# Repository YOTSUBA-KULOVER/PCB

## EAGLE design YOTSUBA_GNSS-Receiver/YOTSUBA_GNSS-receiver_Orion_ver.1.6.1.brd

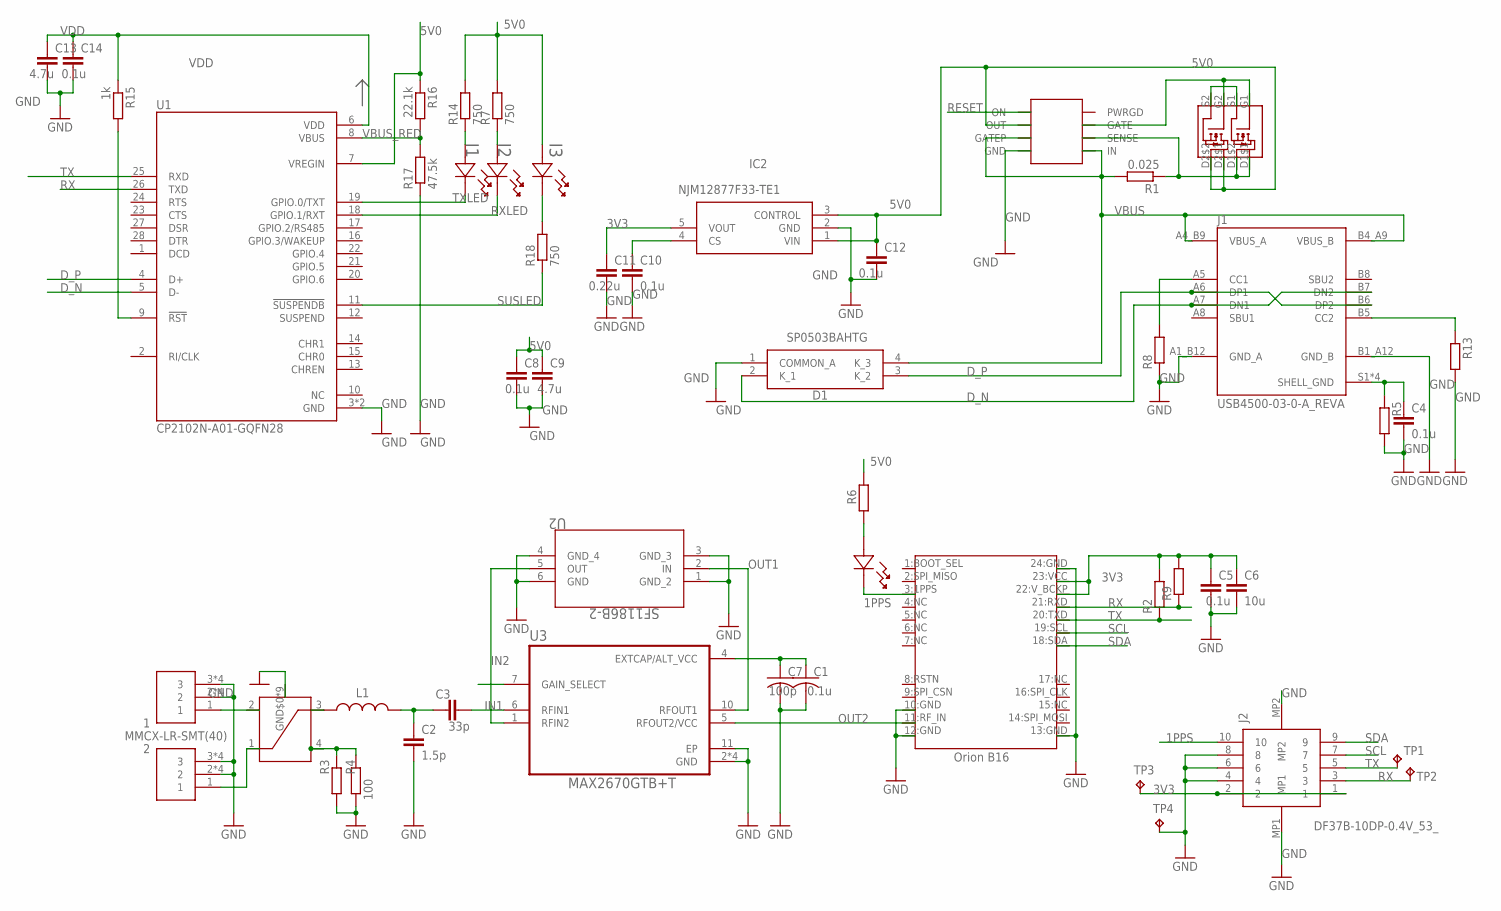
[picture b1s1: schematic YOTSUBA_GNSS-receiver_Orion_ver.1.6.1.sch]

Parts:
1, 2: MMCX-LR-SMT(40)
C1: 0.1u; C1608_OS
C2: 1.5p; C1608
C3: 33p; C1608
C4, C5, C8, C10, C12, C14: 0.1u; C1608
C6: 10u; C1608
C7: 100p; C1608_OS
C9, C13: 4.7u; C1608
C11: 0.22u; C1608
D1: SP0503BAHTG
I1, I2, I3: SML-E12P8WT86; LED_SMLD12_ROM
IC2: NJM12877F33-TE1; SOT95P280X120-5N
J1: USB4500-03-0-A_REVA; GCT_USB4500-03-0-A_REVA
J2: DF37B-10DP-0.4V_53_; DF37B10DP04V53
L1: 4.3n; INDC1608X100N
R1: 0.025; R0603
R2, R5, R6, R8, R9, R13: R-EU_R0603; R0603
R3, R4: 100; R0603
R7, R14, R18: 750; R0603
R10: SML-E12P8WT86; LED_SMLD12_ROM
R15: 1k; R0603
R16: 22.1k; R0603
R17: 47.5k; R0603
TP1, TP2, TP3, TP4: TPTP13SQ; TP13SQ
U1: CP2102N-A01-GQFN28; QFN50P500X500X80-29N
U2: SF1186B-2; SM3030_MUR
U3: MAX2670GTB+T; DFN300X300X80-11N
U$1: ORION_B16
U$3: HC125.A
U$7: DMG6898LSD; SOIC127P600X150-8N
U$8: LTC4361; SOP65P280X100-8N

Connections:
1PPS: J2.10, R10.1, U$1.3:1PPS
3V3: C5.1, C6.1, C11.1, IC2.5 (VOUT), J2.1, J2.2, R2.2, R9.2, TP3.TP, U$1.22:V_BCKP, U$1.23:VCC
5V0: C8.1, C9.1, C12.1, I3.2, IC2.1 (VIN), IC2.3 (CONTROL), R6.2, R7.2, R14.2, R16.1, U1.7 (VREGIN), U$7.D2$1, U$7.D2$2, U$8.OUT
$11: C1.1, C7.1, U3.4 (EXTCAP/ALT_VCC)
D_N: D1.2 (K_1), J1.A7 (DN1), J1.B7 (DN2), U1.5 (D-)
D_P: D1.3 (K_2), J1.A6 (DP1), J1.B6 (DP2), U1.4 (D+)
GND: 1.2, 1.3, 1.4 (2), 1.5 (3), 1.P$1 (2), 1.P$2 (2), 1.P$3 (3), 1.P$4 (3), 2.2, 2.3, 2.4 (2), 2.5 (3), 2.P$1 (2), 2.P$2 (2), 2.P$3 (3), 2.P$4 (3), C1.2, C2.2, C4.2, C5.2, C6.2, C7.2, C8.2, C9.2, C10.2, C11.2, C12.2, C13.2, C14.2, D1.1 (COMMON_A), IC2.2 (GND), J1.A1_B12 (GND_A), J1.B1_A12 (GND_B), J2.4, J2.6, J2.8, J2.MP1, J2.MP2, R3.1, R4.1, R5.2, R8.1, R13.2, R17.1, TP4.TP, U1.3 (GND), U1.29 (GND), U2.1 (GND_2), U2.3 (GND_3), U2.4 (GND_4), U2.6 (GND), U3.2 (GND), U3.3 (GND), U3.8 (GND), U3.9 (GND), U3.11 (EP), U$1.10:GND, U$1.12:GND, U$1.13:GND, U$1.24:GND, U$3.GND$0 (GND), U$3.GND$1 (GND), U$3.GND$2 (GND), U$3.GND$3 (GND), U$3.GND$4 (GND), U$3.GND$5 (GND), U$3.GND$6 (GND), U$3.GND$7 (GND), U$3.GND$8 (GND), U$8.GND
IN1: C3.2, U3.6 (RFIN1)
IN1_2: C2.1, C3.1, L1.2
IN1_3: L1.1, U$3.3
IN2: U2.5 (OUT), U3.1 (RFIN2)
unnamed: 1.1, U$3.2
unnamed: 2.1, U$3.1
unnamed: I3.1, R18.2
unnamed: C10.1, IC2.4 (CS)
unnamed: I2.2, R7.1
unnamed: C4.1, J1.S1 (SHELL_GND), J1.S2 (SHELL_GND), J1.S3 (SHELL_GND), J1.S4 (SHELL_GND), R5.1
unnamed: I1.2, R14.1
unnamed: R3.2, R4.2, U$3.4
unnamed: R6.1, R10.2
unnamed: U$7.S1, U$7.S2
unnamed: R1.1, U$7.D1$1, U$7.D1$2, U$8.SENSE
unnamed: J1.B5 (CC2), R13.1
unnamed: U$7.G1, U$7.G2, U$8.GATE
unnamed: J1.A5 (CC1), R8.2
unnamed: R15.2, U1.9 (!RST)
OUT1: U2.2 (IN), U3.10 (RFOUT1)
OUT2: U3.5 (RFOUT2/VCC), U$1.11:RF_IN
RESET: U$8.ON
RX: J2.3, R9.1, TP2.TP, U1.26 (TXD), U$1.21:RXD
RXLED: I2.1, U1.18 (GPIO.1/RXT)
SCL: J2.7, U$1.19:SCL
SDA: J2.9, U$1.18:SDA
SUSLED: R18.1, U1.11 (!SUSPENDB)
TX: J2.5, R2.1, TP1.TP, U1.25 (RXD), U$1.20:TXD
TXLED: I1.1, U1.19 (GPIO.0/TXT)
VBUS: D1.4 (K_3), J1.A4_B9 (VBUS_A), J1.B4_A9 (VBUS_B), R1.2, U$8.GATEP, U$8.IN
VBUS_RED: R16.2, R17.2, U1.8 (VBUS)
VDD: C13.1, C14.1, R15.1, U1.6 (VDD)

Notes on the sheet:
Orion B16

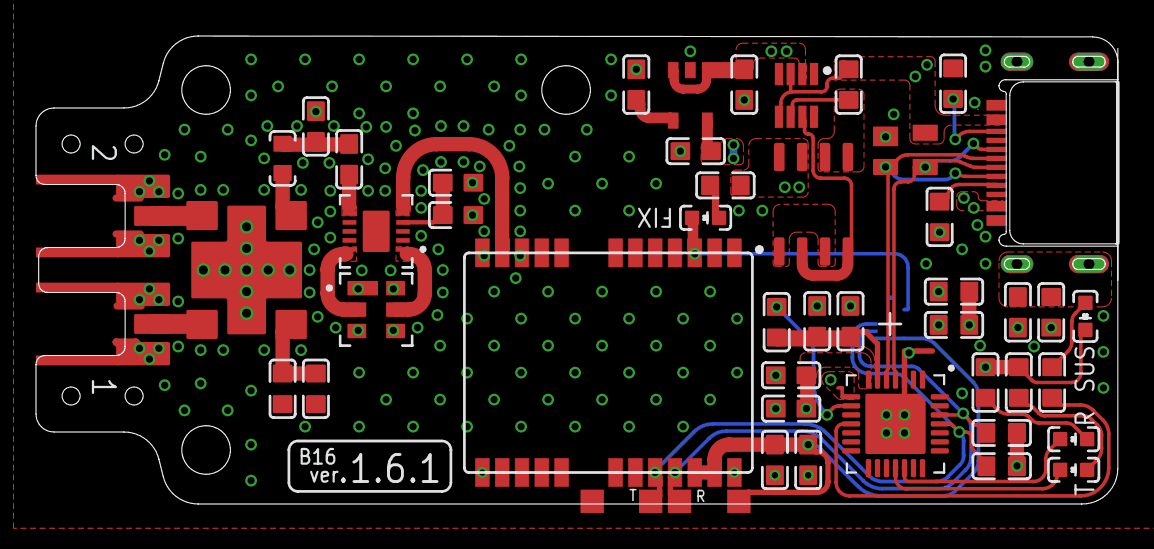
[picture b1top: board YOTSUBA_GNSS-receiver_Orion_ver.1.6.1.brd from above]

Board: 4 copper layers, 60.1 x 26.0 mm, 51 parts (1 on the bottom side), 38 nets.

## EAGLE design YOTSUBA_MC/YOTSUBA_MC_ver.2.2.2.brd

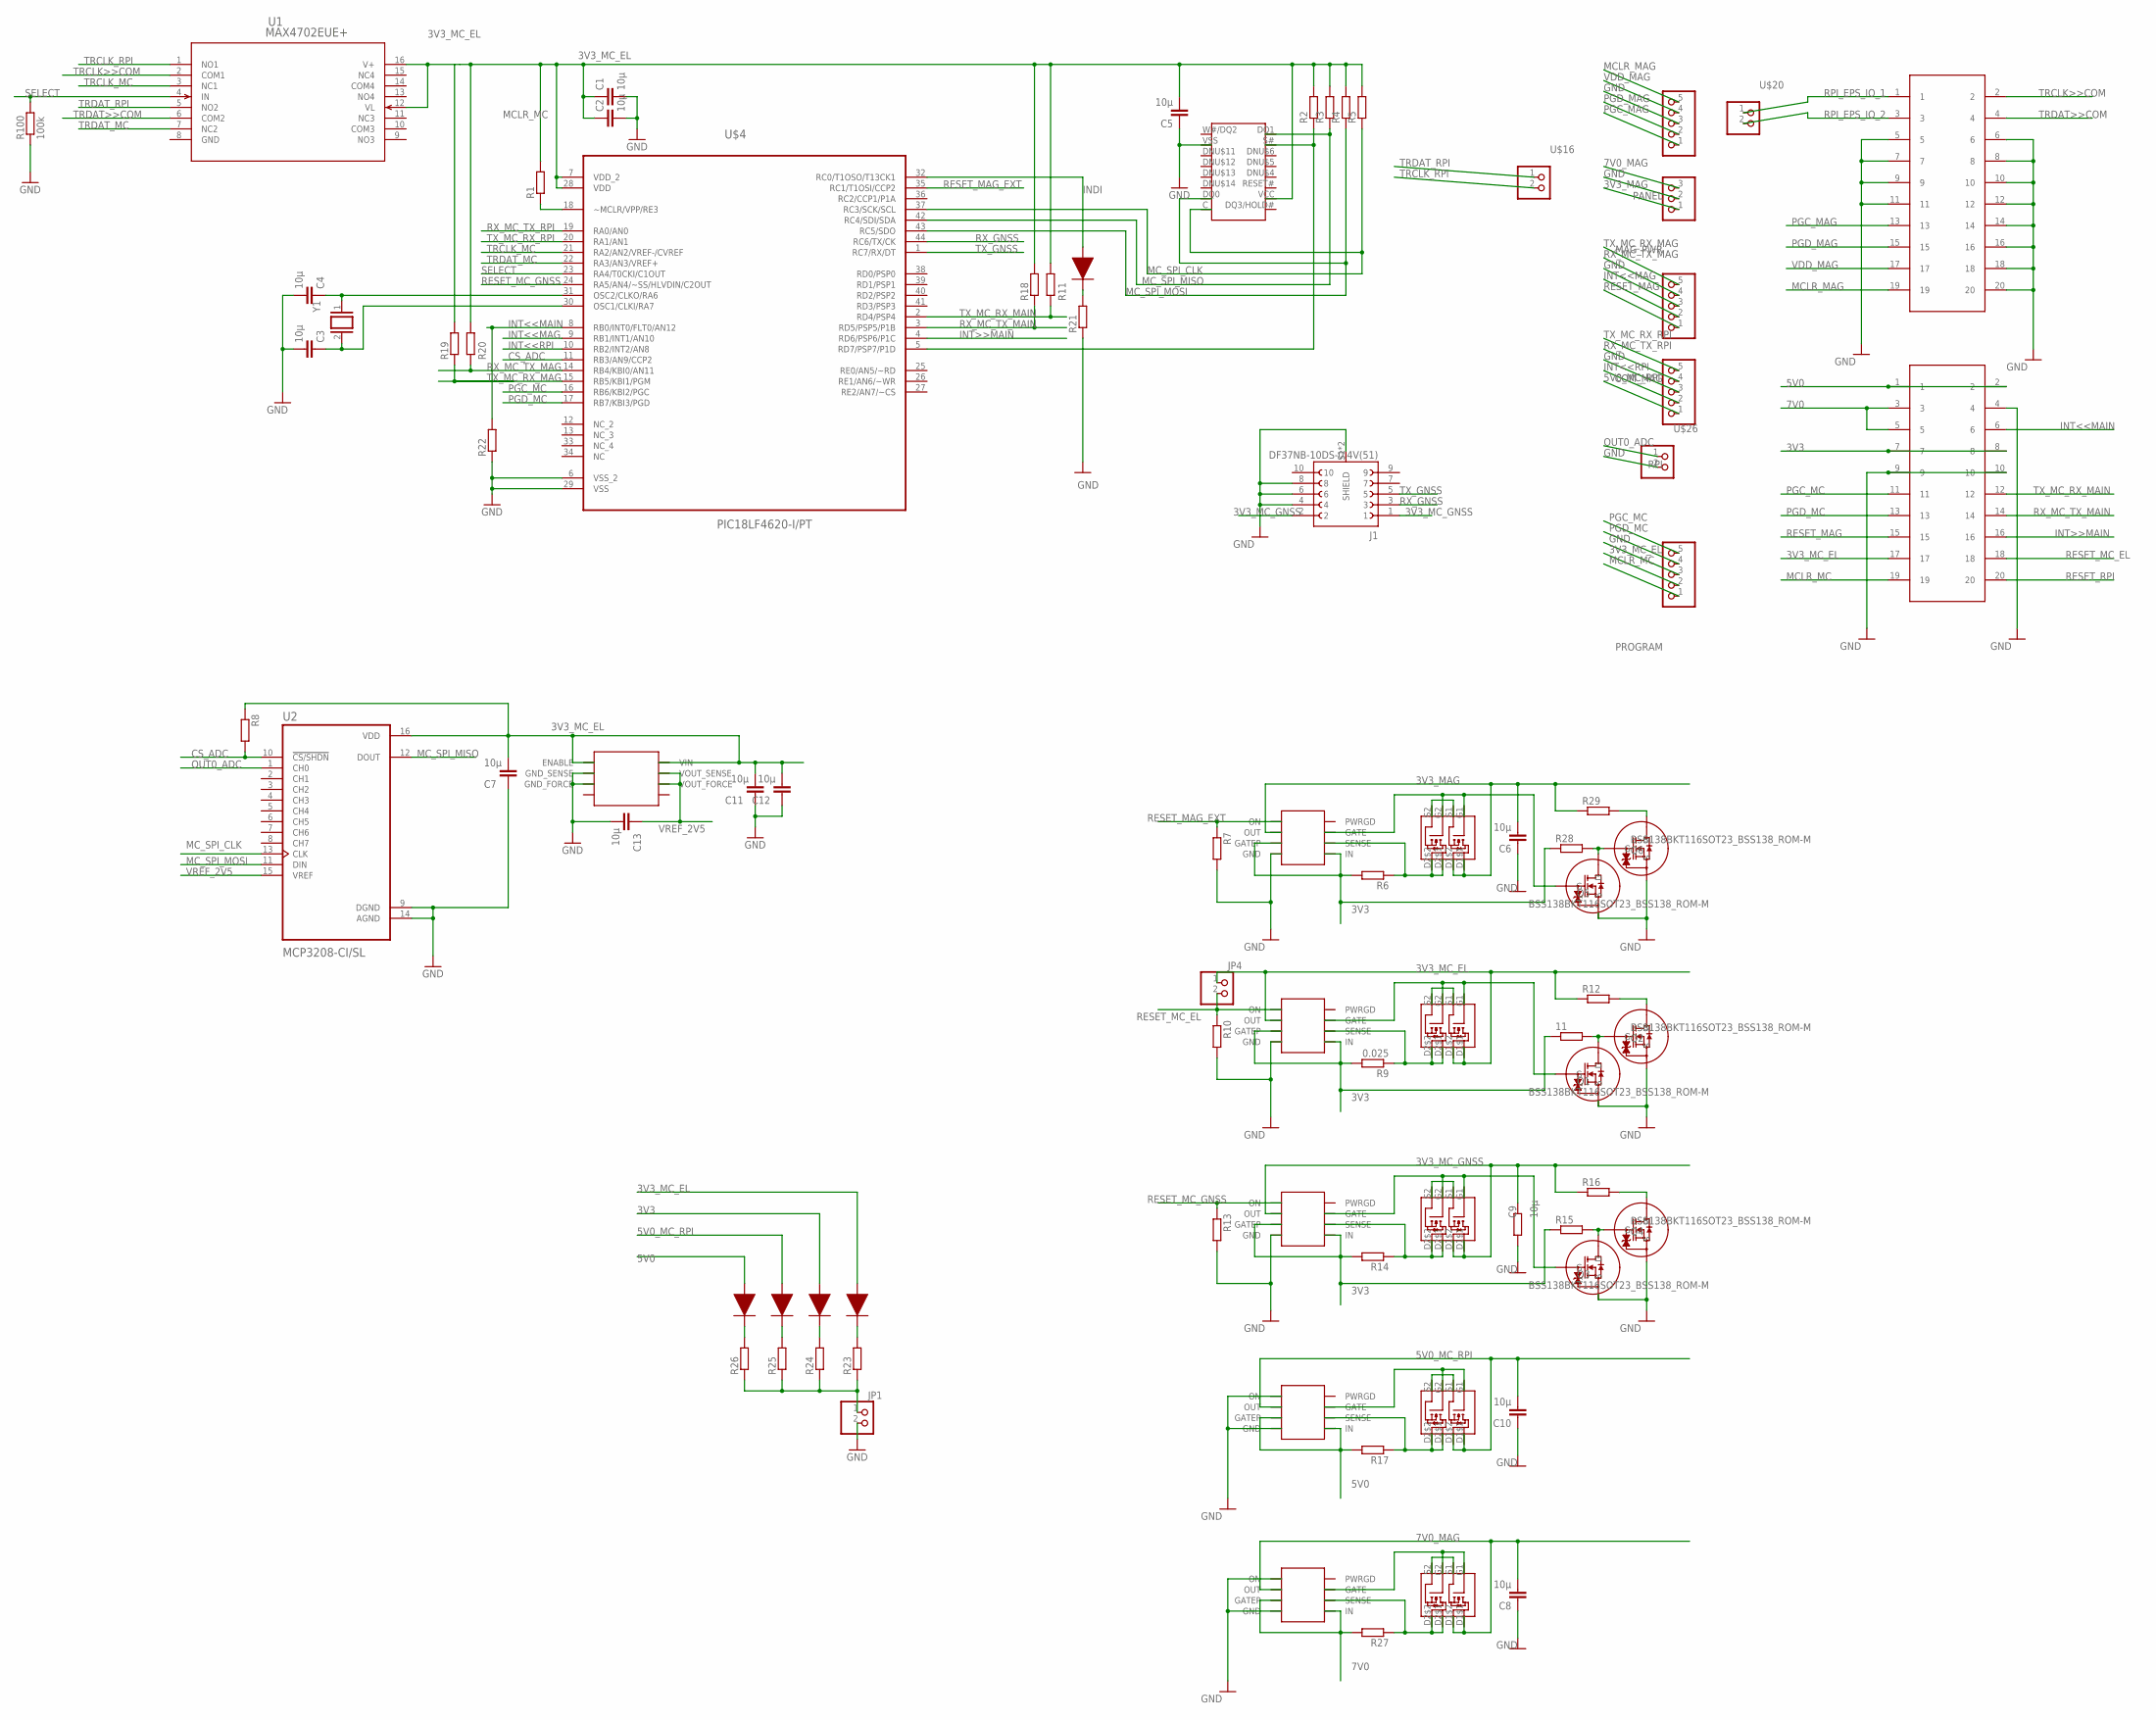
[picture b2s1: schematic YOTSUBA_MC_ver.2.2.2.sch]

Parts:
11: R-EU_R2012; R2012
C1, C2, C3, C4, C5, C6, C7, C8, C10, C11, C12, C13: 10μ; C2012
C9: 10μ; R2012
COM_MAG: PINHD-1X5; 1X05
J1: DF37NB-10DS-0.4V(51); HRS_DF37NB-10DS-0.4V(51)
JP1, JP4: PINHD-1X2; 1X02
MAG_PWR: PINHD-1X3; 1X03
PANEL: PINHD-1X5; 1X05
PROGRAM: PINHD-1X5; 1X05
Q1, Q2, Q3, Q4, Q5, Q6: BSS138BKT116SOT23_BSS138_ROM-M; SOT23_BSS138_ROM-M
R1, R2, R3, R4, R5, R6, R7, R8, R10, R11, R12, R13, R14, R15, R16, R17, R18, R19, R20, R21, R22, R23, R24, R25, R26, R27, R28, R29: R-EU_R2012; R2012
R9: 0.025; R2012
R100: 100k; R2012
RPI: PINHD-1X5; 1X05
U1: MAX4702EUE+; 21-0066J_16
U2: MCP3208-CI/SL; SOIC127P600X175-16N
U$1: MT25QL512_16SOP2; SOIC127P1032X265-16N
U$2, U$7, U$9, U$10, U$13: DMG6898LSD; SOIC127P600X150-8N
U$3, U$8, U$11, U$12, U$14: LTC4361; SOP65P280X100-8N
U$4: PIC18LF4620-I/PT; QFP80P1200X1200X120-44N
U$16, U$20, U$26: PINHD-1X2; 1X02
U$17, U$22: M50-3001045
U$18, U$21, U$23, U$24, U$25: LED_1608
U$19: ADR35XX; SOP65P490X110-8N
Y1: HC-49/U-S16000000ABJB; XTAL_HC49P488W43L1150T466H350

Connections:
3V3: 11.1, R6.2, R9.2, R14.2, R15.1, R28.1, U$3.GATEP, U$3.IN, U$8.GATEP, U$8.IN, U$11.GATEP, U$11.IN, U$17.7, U$17.8, U$23.A
3V3_MAG: C6.2, MAG_PWR.1, R29.1, U$2.D1$1, U$2.D1$2, U$3.OUT
3V3_MC_EL: C1.1, C2.1, C5.2, C7.2, C11.2, C12.2, JP4.1, PROGRAM.2, R1.2, R2.2, R3.2, R4.2, R5.2, R8.1, R11.2, R12.1, R18.2, R19.2, R20.2, U1.12 (VL), U1.16 (V+), U2.16 (VDD), U$1.VCC, U$4.7 (VDD_2), U$4.28 (VDD), U$7.D1$1, U$7.D1$2, U$8.OUT, U$17.17, U$19.ENABLE, U$19.VIN, U$21.A
3V3_MC_GNSS: C9.2, J1.1, J1.2, R16.1, U$10.D1$1, U$10.D1$2, U$11.OUT
5V0: R17.2, U$14.GATEP, U$14.IN, U$17.1, U$17.2, U$25.A
5V0_MC_RPI: C10.2, RPI.1, U$13.D1$1, U$13.D1$2, U$14.OUT, U$24.A
7V0: R27.2, U$12.GATEP, U$12.IN, U$17.3, U$17.5
7V0_MAG: C8.2, MAG_PWR.3, U$9.D1$1, U$9.D1$2, U$12.OUT
CS_ADC: R8.2, U2.10 (!CS/SHDN), U$4.11 (RB3/AN9/CCP2)
GND: C1.2, C2.2, C3.2, C4.2, C5.1, C6.1, C7.1, C8.1, C9.1, C10.1, C11.1, C12.1, C13.2, COM_MAG.3, J1.4, J1.6, J1.8, J1.S1 (SHIELD), J1.S2 (SHIELD), JP1.2, MAG_PWR.2, PANEL.3, PROGRAM.3, Q1.1 (S), Q2.1 (S), Q3.1 (S), Q4.1 (S), Q5.1 (S), Q6.1 (S), R7.2, R10.2, R13.2, R21.1, R22.1, R100.1, RPI.3, U1.8 (GND), U2.9 (DGND), U2.14 (AGND), U$1.VSS, U$3.GND, U$4.6 (VSS_2), U$4.29 (VSS), U$8.GND, U$11.GND, U$12.GND, U$12.ON, U$14.GND, U$14.ON, U$17.4, U$17.9, U$17.10, U$19.GND_FORCE, U$19.GND_SENSE, U$22.5, U$22.6, U$22.7, U$22.8, U$22.9, U$22.10, U$22.11, U$22.12, U$22.14, U$22.16, U$22.18, U$22.20, U$26.2
INDI: U$4.32 (RC0/T1OSO/T13CK1), U$18.A
INT<<MAG: COM_MAG.2, U$4.9 (RB1/INT1/AN10)
INT<<MAIN: R22.2, U$4.8 (RB0/INT0/FLT0/AN12), U$17.6
INT<<RPI: RPI.2, U$4.10 (RB2/INT2/AN8)
INT>>MAIN: U$4.4 (RD6/PSP6/P1C), U$17.16
MCLR_MAG: PANEL.5, U$22.19
MCLR_MC: PROGRAM.1, R1.1, U$4.18 (~MCLR/VPP/RE3), U$17.19
MC_SPI_CLK: R5.1, U2.13 (CLK), U$1.C, U$4.37 (RC3/SCK/SCL)
MC_SPI_MISO: R3.1, U2.12 (DOUT), U$1.DQ1, U$4.42 (RC4/SDI/SDA)
MC_SPI_MOSI: R4.1, U2.11 (DIN), U$1.DQ0, U$4.43 (RC5/SDO)
unnamed: R23.2, U$21.C
unnamed: C3.1, U$4.30 (OSC1/CLKI/RA7), Y1.2
unnamed: R24.2, U$23.C
unnamed: C4.1, U$4.31 (OSC2/CLKO/RA6), Y1.1
unnamed: R25.2, U$24.C
unnamed: R26.2, U$25.C
unnamed: R2.1, U$1.S#, U$4.5 (RD7/PSP7/P1D)
unnamed: JP1.1, R23.1, R24.1, R25.1, R26.1
unnamed: U$2.S1, U$2.S2
unnamed: R6.1, U$2.D2$1, U$2.D2$2, U$3.SENSE
unnamed: Q5.2 (G), U$2.G1, U$2.G2, U$3.GATE
unnamed: Q5.3 (D), Q6.2 (G), R28.2
unnamed: U$9.S1, U$9.S2
unnamed: R21.2, U$18.C
unnamed: R27.1, U$9.D2$1, U$9.D2$2, U$12.SENSE
unnamed: U$9.G1, U$9.G2, U$12.GATE
unnamed: Q6.3 (D), R29.2
unnamed: U$7.S1, U$7.S2
unnamed: R9.1, U$7.D2$1, U$7.D2$2, U$8.SENSE
unnamed: Q1.2 (G), U$7.G1, U$7.G2, U$8.GATE
unnamed: 11.2, Q1.3 (D), Q2.2 (G)
unnamed: Q2.3 (D), R12.2
unnamed: U$10.S1, U$10.S2
unnamed: R14.1, U$10.D2$1, U$10.D2$2, U$11.SENSE
unnamed: Q3.2 (G), U$10.G1, U$10.G2, U$11.GATE
unnamed: Q3.3 (D), Q4.2 (G), R15.2
unnamed: Q4.3 (D), R16.2
unnamed: U$13.S1, U$13.S2
unnamed: R17.1, U$13.D2$1, U$13.D2$2, U$14.SENSE
unnamed: U$13.G1, U$13.G2, U$14.GATE
OUT0_ADC: U2.1 (CH0), U$26.1
PGC_MAG: PANEL.1, U$22.13
PGC_MC: PROGRAM.5, U$4.16 (RB6/KBI2/PGC), U$17.11
PGD_MAG: PANEL.2, U$22.15
PGD_MC: PROGRAM.4, U$4.17 (RB7/KBI3/PGD), U$17.13
RESET_MAG: COM_MAG.1, U$17.15
RESET_MAG_EXT: R7.1, U$3.ON, U$4.35 (RC1/T1OSI/CCP2)
RESET_MC_EL: JP4.2, R10.1, U$8.ON, U$17.18
RESET_MC_GNSS: R13.1, U$4.24 (RA5/AN4/~SS/HLVDIN/C2OUT), U$11.ON
RESET_RPI: U$17.20
RPI_EPS_IO_1: U$20.1, U$22.1
RPI_EPS_IO_2: U$20.2, U$22.3
RX_GNSS: J1.3, U$4.44 (RC6/TX/CK)
RX_MC_TX_MAG: COM_MAG.4, R20.1, U$4.14 (RB4/KBI0/AN11)
RX_MC_TX_MAIN: R18.1, U$4.3 (RD5/PSP5/P1B), U$17.14
RX_MC_TX_RPI: RPI.4, U$4.19 (RA0/AN0)
SELECT: R100.2, U1.4 (IN), U$4.23 (RA4/T0CKI/C1OUT)
TRCLK>>COM: U1.2 (COM1), U$22.2
TRCLK_MC: U1.3 (NC1), U$4.21 (RA2/AN2/VREF-/CVREF)
TRCLK_RPI: U1.1 (NO1), U$16.1
TRDAT>>COM: U1.6 (COM2), U$22.4
TRDAT_MC: U1.7 (NC2), U$4.22 (RA3/AN3/VREF+)
TRDAT_RPI: U1.5 (NO2), U$16.2
TX_GNSS: J1.5, U$4.1 (RC7/RX/DT)
TX_MC_RX_MAG: COM_MAG.5, R19.1, U$4.15 (RB5/KBI1/PGM)
TX_MC_RX_MAIN: R11.1, U$4.2 (RD4/PSP4), U$17.12
TX_MC_RX_RPI: RPI.5, U$4.20 (RA1/AN1)
VDD_MAG: PANEL.4, U$22.17
VREF_2V5: C13.1, U2.15 (VREF), U$19.VOUT_FORCE, U$19.VOUT_SENSE

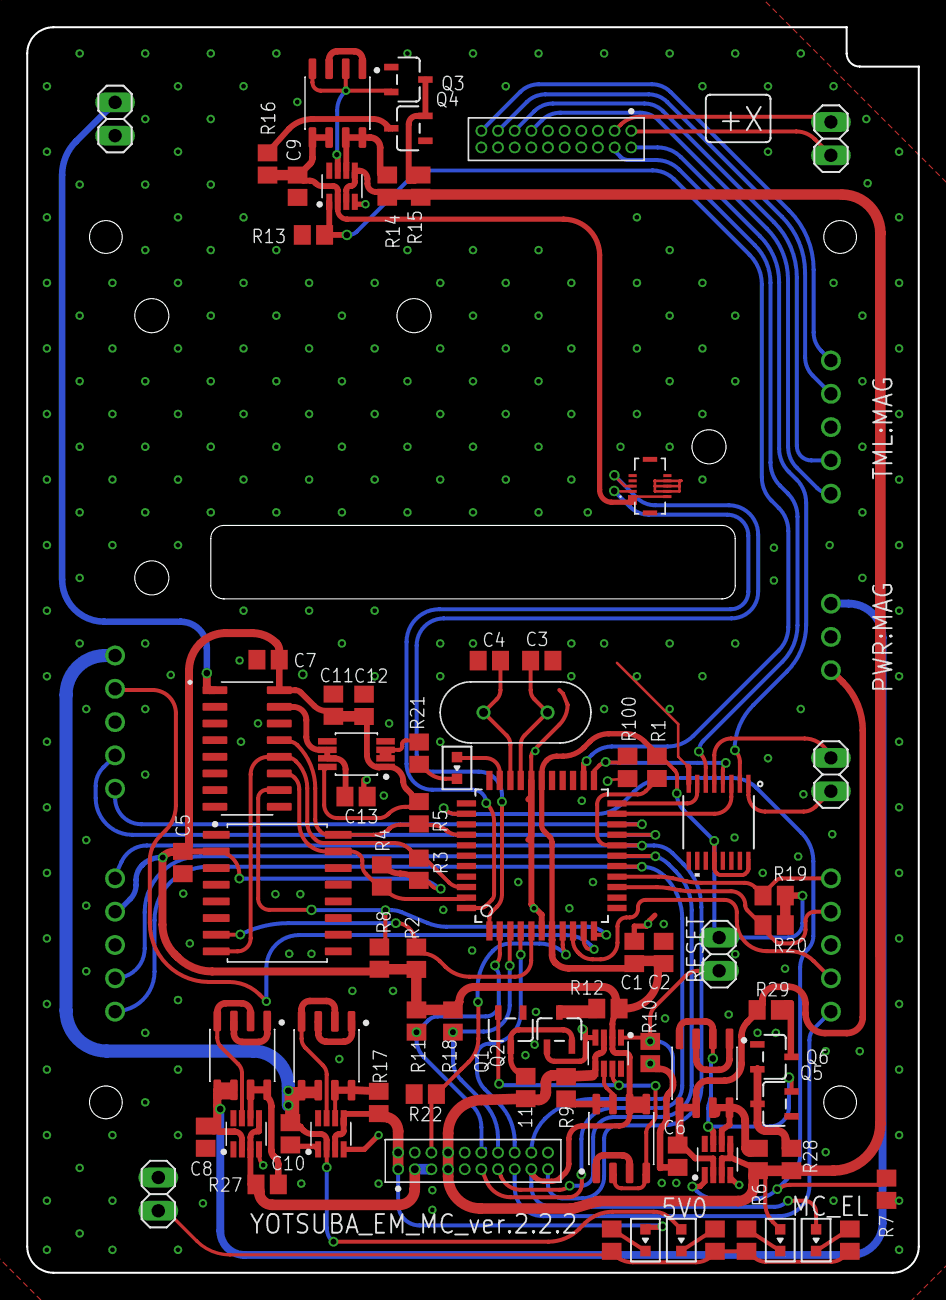
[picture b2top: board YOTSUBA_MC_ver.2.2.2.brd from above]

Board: 2 copper layers, 68.0 x 95.0 mm, 84 parts (0 on the bottom side), 78 nets.

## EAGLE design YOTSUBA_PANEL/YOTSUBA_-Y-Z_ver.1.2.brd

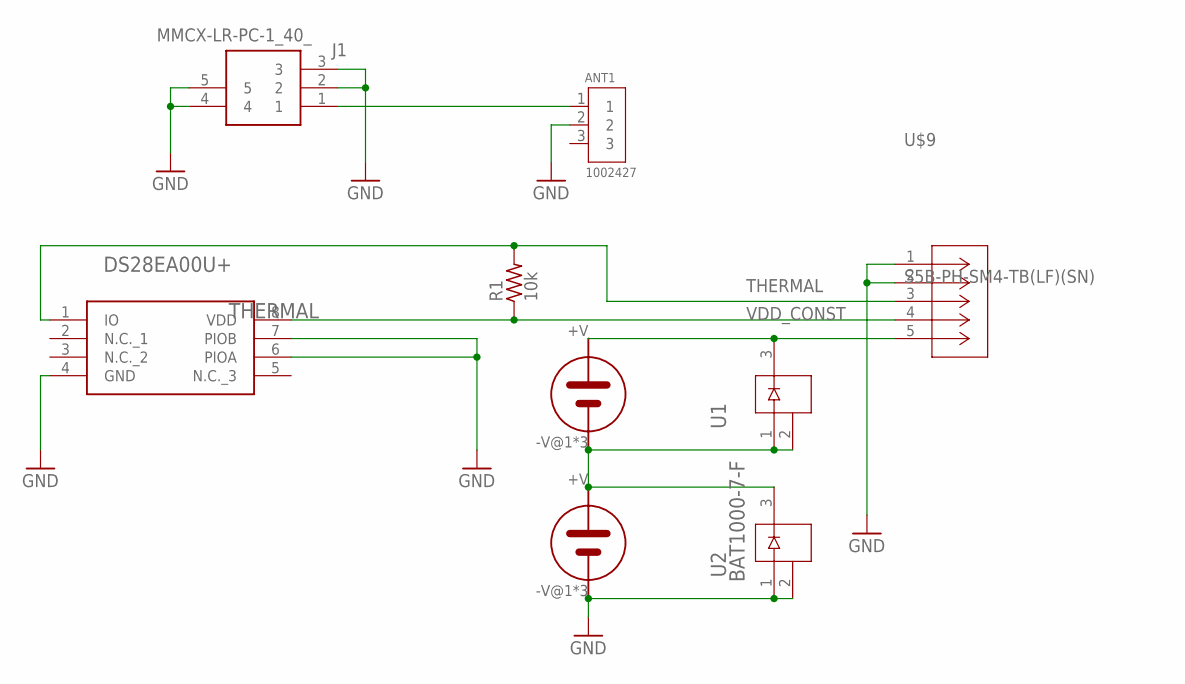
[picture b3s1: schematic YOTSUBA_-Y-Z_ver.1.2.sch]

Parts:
ANT1: 1002427; ANTENNA_1002427
J1: MMCX-LR-PC-1_40_; MMCXLRPC140
R1: 10k; R0805
THERMAL: DS28EA00U+; SOP65P490X110-8N
U1, U2: BAT1000-7-F; SOT23_BAT_DIO
U$2, U$3: 3G30A; SOLAR_3G30A
U$9: S5B-PH-SM4-TB(LF)(SN); CONN_S5B-PH-SM4-TB_JST

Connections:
GND: ANT1.2, J1.2, J1.3, J1.4, J1.5, THERMAL.4 (GND), THERMAL.6 (PIOA), THERMAL.7 (PIOB), U2.1, U2.2, U$3.-V@1 (-V), U$3.-V@2 (-V), U$3.-V@3 (-V), U$9.1, U$9.2
unnamed: U1.1, U1.2, U2.3, U$2.-V@1 (-V), U$2.-V@2 (-V), U$2.-V@3 (-V), U$3.+V
unnamed: U1.3, U$2.+V, U$9.5
RF2: ANT1.1, J1.1
THERMAL: R1.2, THERMAL.1 (IO), U$9.3
VDD_CONST: R1.1, THERMAL.8 (VDD), U$9.4

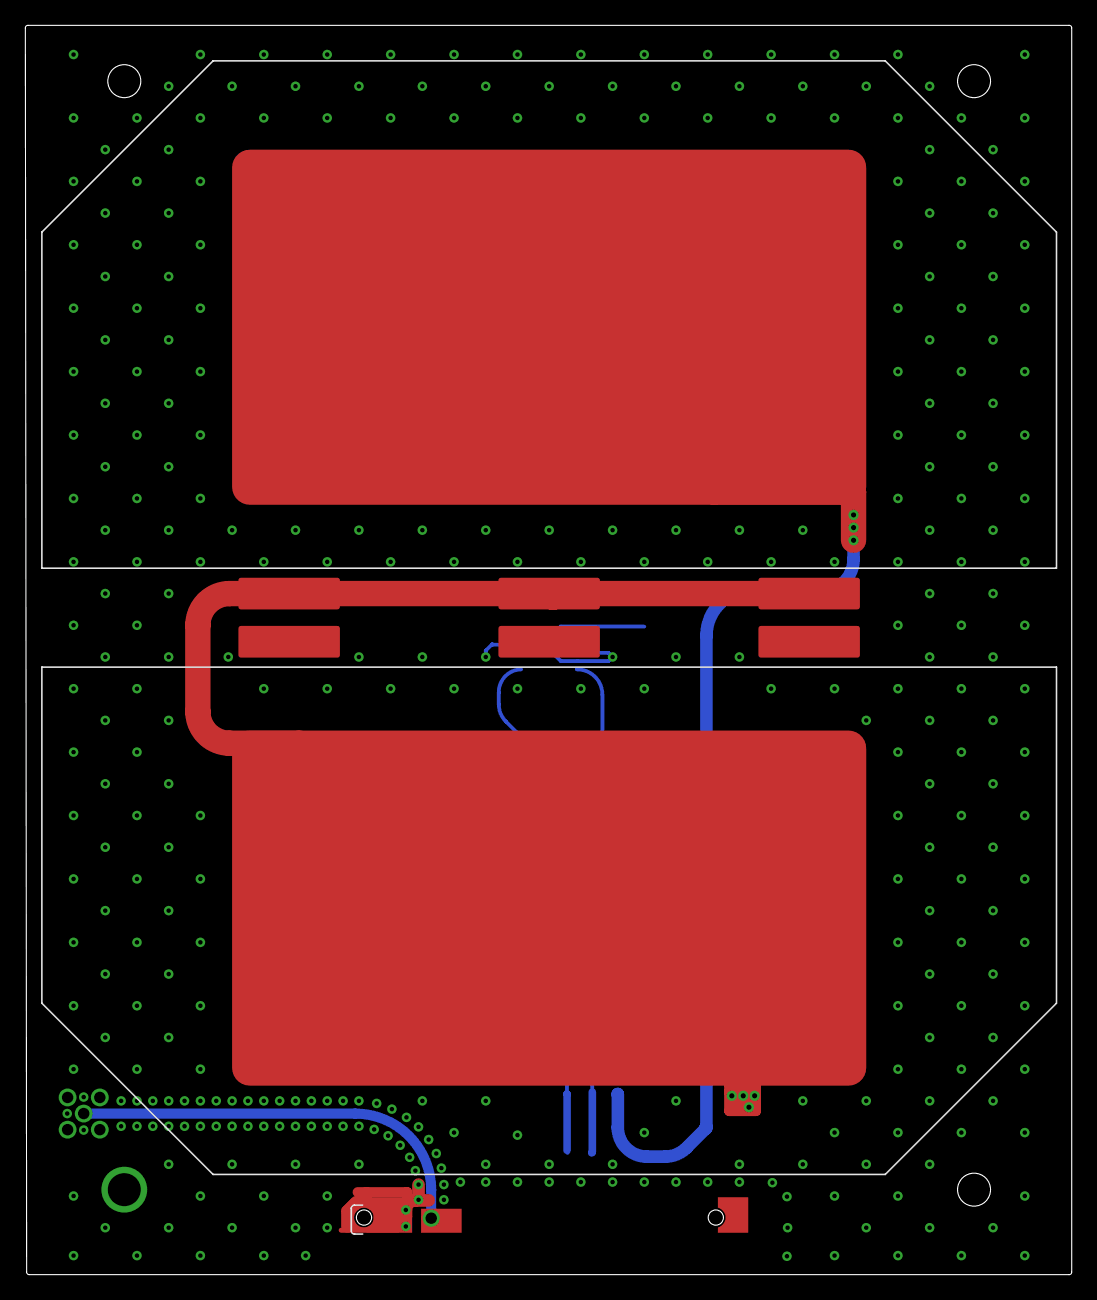
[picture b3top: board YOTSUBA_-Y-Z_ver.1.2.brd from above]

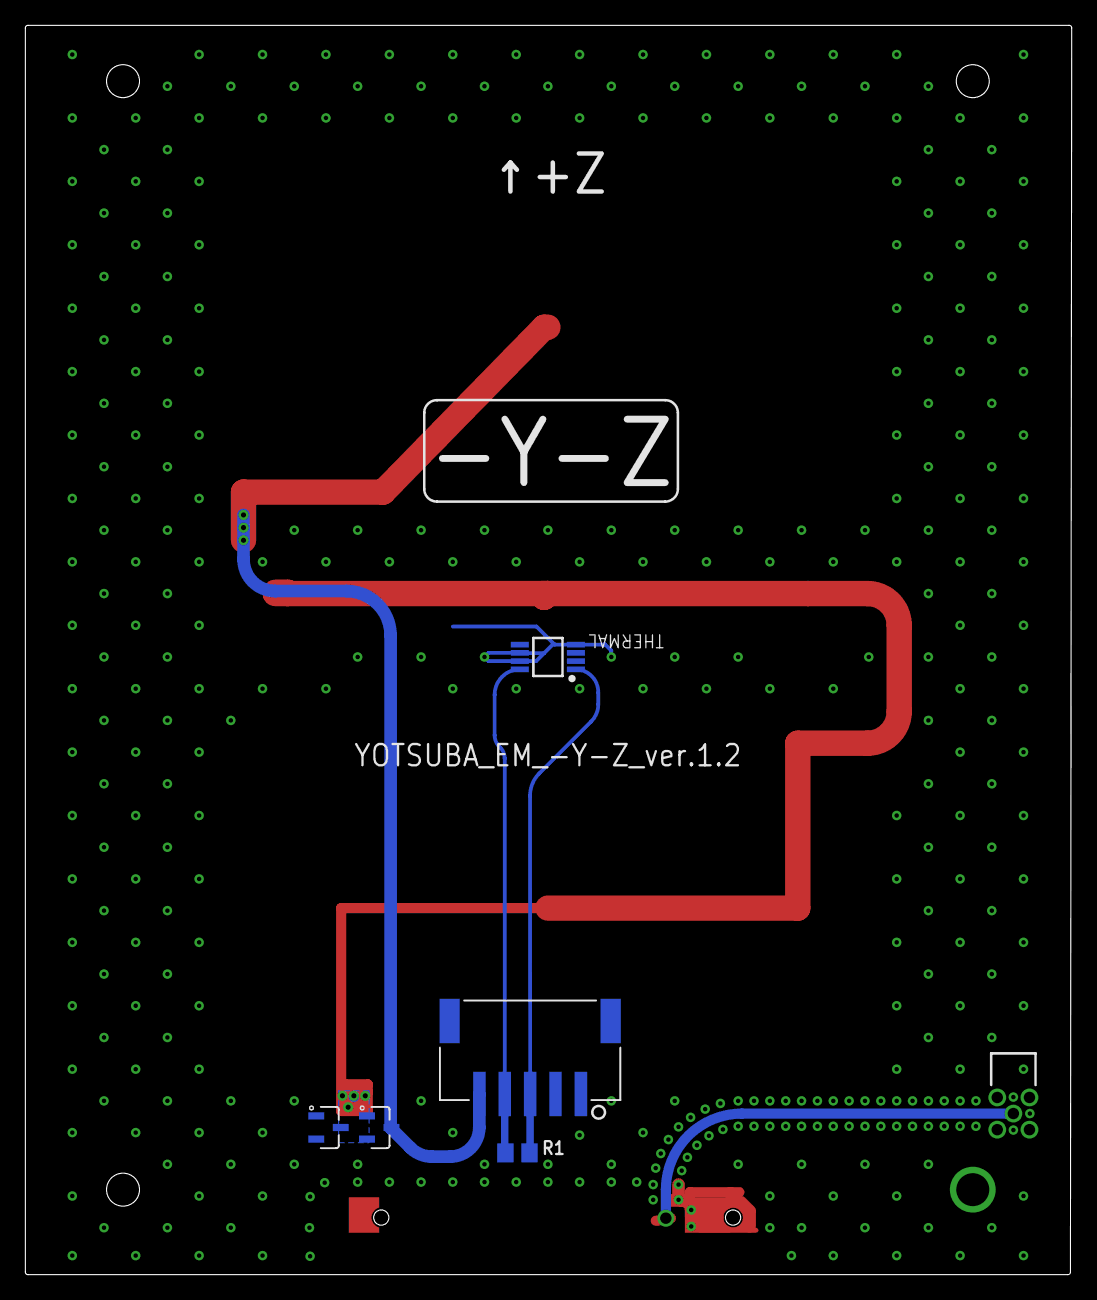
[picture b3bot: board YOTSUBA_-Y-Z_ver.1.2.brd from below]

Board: 2 copper layers, 82.5 x 98.5 mm, 9 parts (6 on the bottom side), 6 nets.

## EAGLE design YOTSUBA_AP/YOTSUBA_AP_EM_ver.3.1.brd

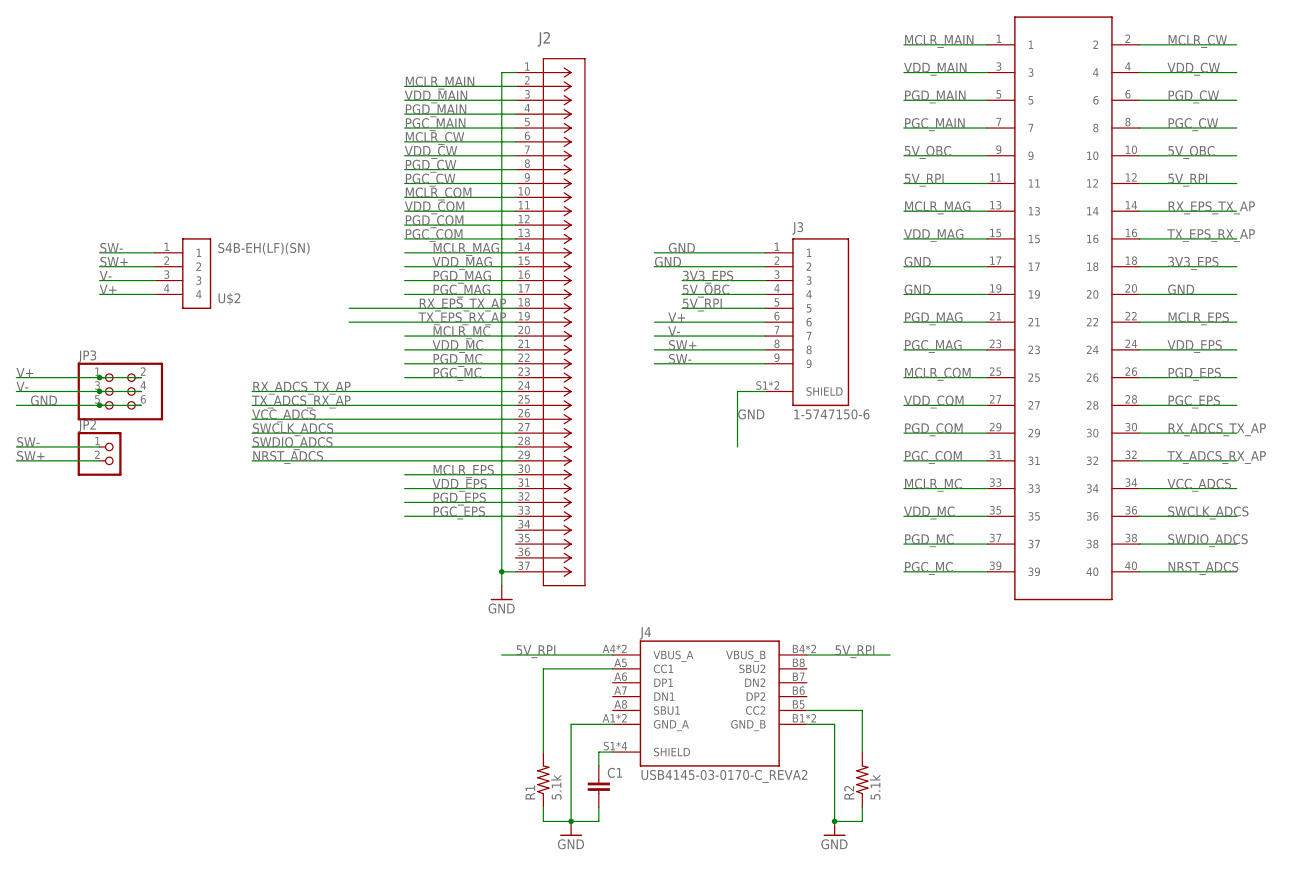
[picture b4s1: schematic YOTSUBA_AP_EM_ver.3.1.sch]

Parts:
C1: C-EUC2012; C2012
J2: 1-5747301-6; CONN_1-5747301-6_TYC
J3: 1-5747150-6; TE_1-5747150-6
J4: USB4145-03-0170-C_REVA2; GCT_USB4145-03-0170-C_REVA2
JP2: PINHD-1X2; 1X02
JP3: PINHD-2X3; 2X03
R1, R2: 5.1k; R0805
U$1: M50-3902042
U$2: S4B-EH(LF)(SN); JST_S4B-EH(LF)(SN)

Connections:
3V3_EPS: J3.3, U$1.18
5V_OBC: J3.4, U$1.9, U$1.10
5V_RPI: J3.5, J4.A4 (VBUS_A), J4.A9 (VBUS_A), J4.B4 (VBUS_B), J4.B9 (VBUS_B), U$1.11, U$1.12
GND: C1.2, J2.1, J2.37, J3.1, J3.2, J3.S1 (SHIELD), J3.S2 (SHIELD), J4.A1 (GND_A), J4.A12 (GND_A), J4.B1 (GND_B), J4.B12 (GND_B), JP3.5, JP3.6, R1.1, R2.1, U$1.17, U$1.19, U$1.20
MCLR_COM: J2.10, U$1.25
MCLR_CW: J2.6, U$1.2
MCLR_EPS: J2.30, U$1.22
MCLR_MAG: J2.14, U$1.13
MCLR_MAIN: J2.2, U$1.1
MCLR_MC: J2.20, U$1.33
unnamed: C1.1, J4.S1 (SHIELD), J4.S2 (SHIELD), J4.S3 (SHIELD), J4.S4 (SHIELD)
unnamed: J4.A5 (CC1), R1.2
unnamed: J4.B5 (CC2), R2.2
NRST_ADCS: J2.29, U$1.40
PGC_COM: J2.13, U$1.31
PGC_CW: J2.9, U$1.8
PGC_EPS: J2.33, U$1.28
PGC_MAG: J2.17, U$1.23
PGC_MAIN: J2.5, U$1.7
PGC_MC: J2.23, U$1.39
PGD_COM: J2.12, U$1.29
PGD_CW: J2.8, U$1.6
PGD_EPS: J2.32, U$1.26
PGD_MAG: J2.16, U$1.21
PGD_MAIN: J2.4, U$1.5
PGD_MC: J2.22, U$1.37
RX_ADCS_TX_AP: J2.24, U$1.30
RX_EPS_TX_AP: J2.18, U$1.14
SW+: J3.8, JP2.2, U$2.2
SW-: J3.9, JP2.1, U$2.1
SWCLK_ADCS: J2.27, U$1.36
SWDIO_ADCS: J2.28, U$1.38
TX_ADCS_RX_AP: J2.25, U$1.32
TX_EPS_RX_AP: J2.19, U$1.16
V+: J3.6, JP3.1, JP3.2, U$2.4
V-: J3.7, JP3.3, JP3.4, U$2.3
VCC_ADCS: J2.26, U$1.34
VDD_COM: J2.11, U$1.27
VDD_CW: J2.7, U$1.4
VDD_EPS: J2.31, U$1.24
VDD_MAG: J2.15, U$1.15
VDD_MAIN: J2.3, U$1.3
VDD_MC: J2.21, U$1.35

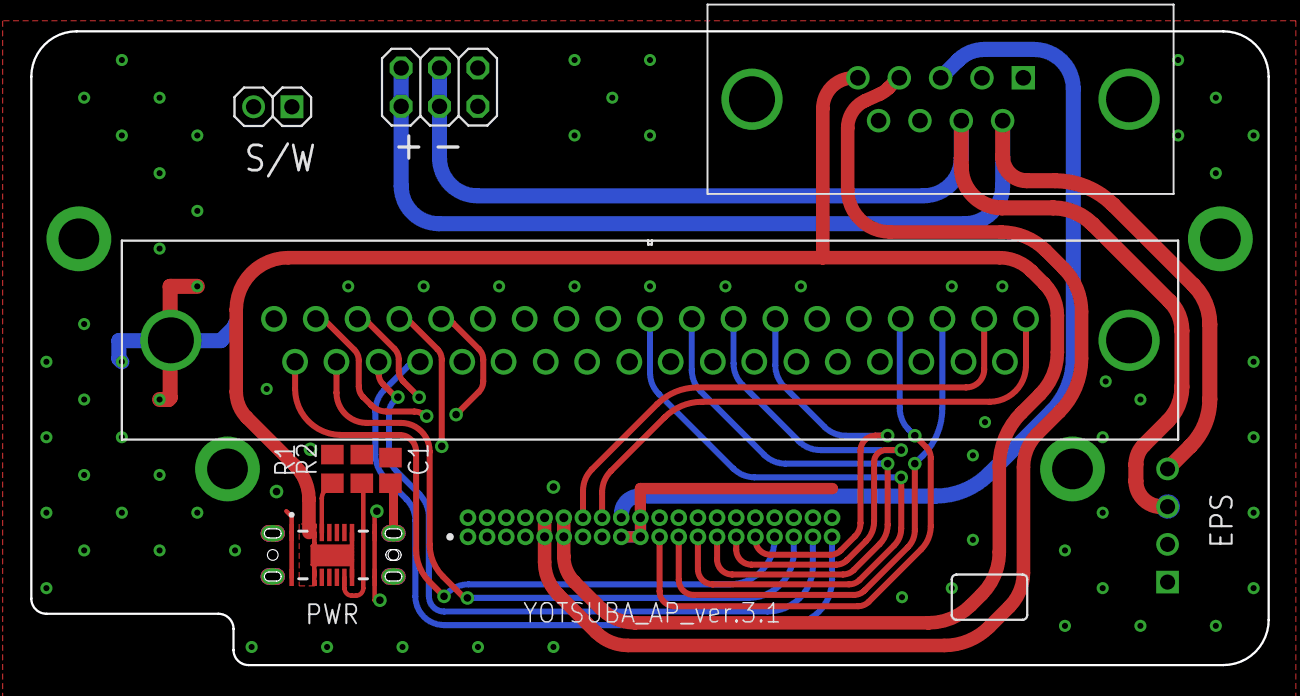
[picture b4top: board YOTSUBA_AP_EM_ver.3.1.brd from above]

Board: 4 copper layers, 82.0 x 42.0 mm, 10 parts (1 on the bottom side), 43 nets.

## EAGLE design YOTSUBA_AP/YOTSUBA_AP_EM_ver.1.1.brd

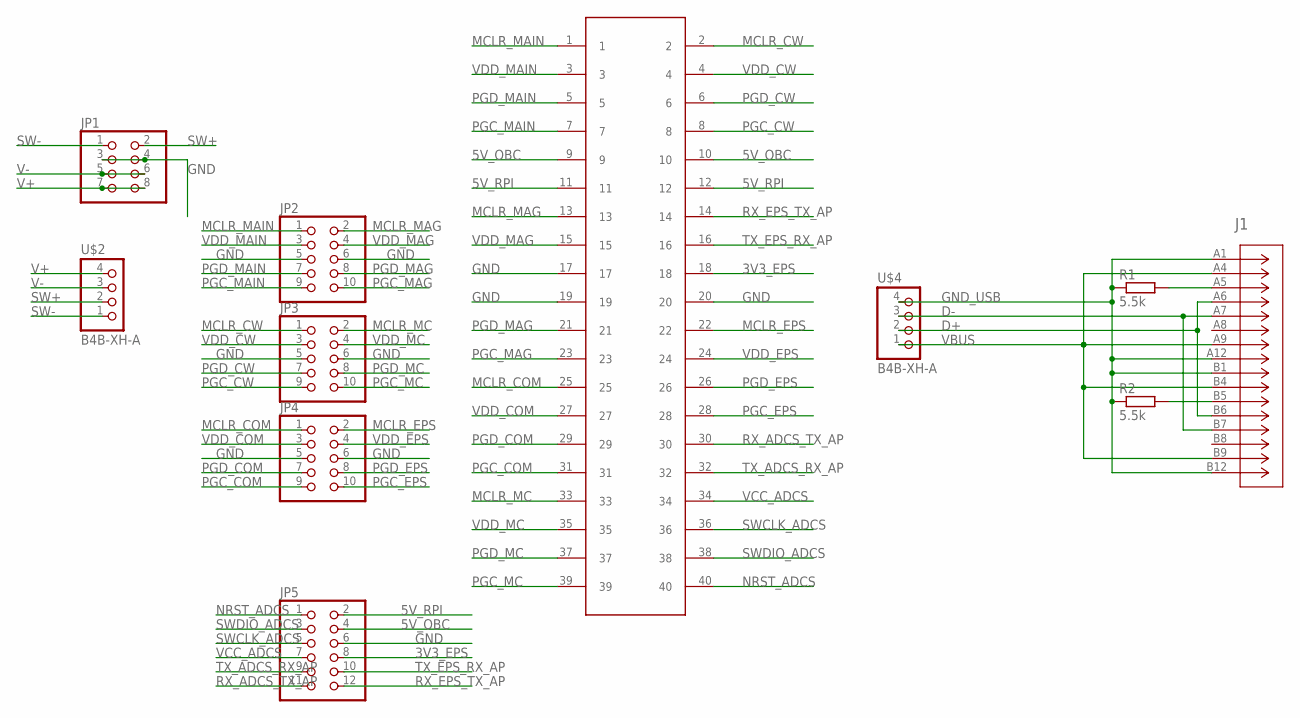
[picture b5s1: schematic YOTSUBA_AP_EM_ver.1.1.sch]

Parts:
J1: 217182-0001; CONN_217182-0001_MOL
JP1: PINHD-2X4; 2X04
JP2, JP3, JP4: PINHD-2X5; 2X05
JP5: PINHD-2X6; 2X06
R1, R2: 5.5k; M2012
U$1: M50-3902042
U$2, U$4: B4B-XH-A

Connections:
3V3_EPS: JP5.8, U$1.18
5V_OBC: JP5.4, U$1.9, U$1.10
5V_RPI: JP5.2, U$1.11, U$1.12
D+: J1.A6 (DP1), J1.B6 (DP2), U$4.2
D-: J1.A7 (DN1), J1.B7 (DN2), U$4.3
GND: JP1.3, JP1.4, JP2.5, JP2.6, JP3.5, JP3.6, JP4.5, JP4.6, JP5.6, U$1.17, U$1.19, U$1.20
GND_USB: J1.A1 (GND_2), J1.A12 (GND_3), J1.B1 (GND_4), J1.B12 (GND), R1.1, R2.1, U$4.4
MCLR_COM: JP4.1, U$1.25
MCLR_CW: JP3.1, U$1.2
MCLR_EPS: JP4.2, U$1.22
MCLR_MAG: JP2.2, U$1.13
MCLR_MAIN: JP2.1, U$1.1
MCLR_MC: JP3.2, U$1.33
unnamed: J1.A5 (CC1), R1.2
unnamed: J1.B5 (CC2), R2.2
NRST_ADCS: JP5.1, U$1.40
PGC_COM: JP4.9, U$1.31
PGC_CW: JP3.9, U$1.8
PGC_EPS: JP4.10, U$1.28
PGC_MAG: JP2.10, U$1.23
PGC_MAIN: JP2.9, U$1.7
PGC_MC: JP3.10, U$1.39
PGD_COM: JP4.7, U$1.29
PGD_CW: JP3.7, U$1.6
PGD_EPS: JP4.8, U$1.26
PGD_MAG: JP2.8, U$1.21
PGD_MAIN: JP2.7, U$1.5
PGD_MC: JP3.8, U$1.37
RX_ADCS_TX_AP: JP5.11, U$1.30
RX_EPS_TX_AP: JP5.12, U$1.14
SW+: JP1.2, U$2.2
SW-: JP1.1, U$2.1
SWCLK_ADCS: JP5.5, U$1.36
SWDIO_ADCS: JP5.3, U$1.38
TX_ADCS_RX_AP: JP5.9, U$1.32
TX_EPS_RX_AP: JP5.10, U$1.16
V+: JP1.7, JP1.8, U$2.4
V-: JP1.5, JP1.6, U$2.3
VBUS: J1.A4 (VBUS_2), J1.A9 (VBUS_3), J1.B4 (VBUS_4), J1.B9 (VBUS), U$4.1
VCC_ADCS: JP5.7, U$1.34
VDD_COM: JP4.3, U$1.27
VDD_CW: JP3.3, U$1.4
VDD_EPS: JP4.4, U$1.24
VDD_MAG: JP2.4, U$1.15
VDD_MAIN: JP2.3, U$1.3
VDD_MC: JP3.4, U$1.35

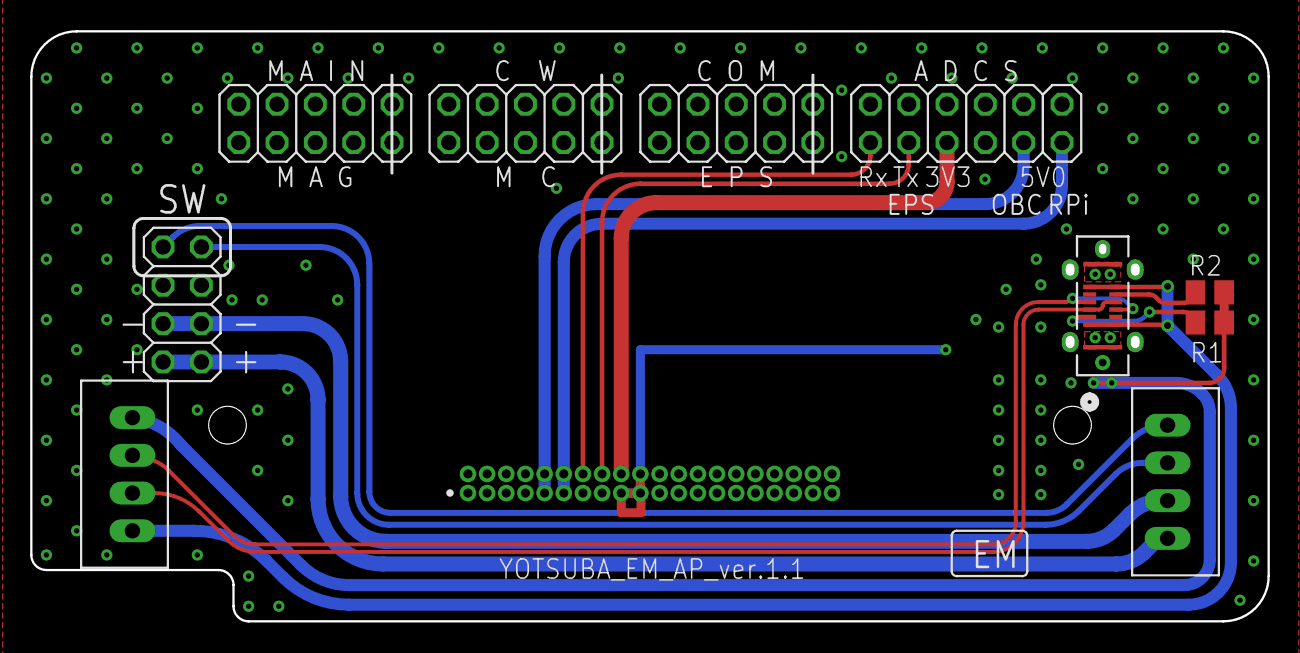
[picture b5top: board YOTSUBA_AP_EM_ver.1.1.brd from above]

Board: 4 copper layers, 81.5 x 38.6 mm, 11 parts (0 on the bottom side), 46 nets.

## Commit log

2023-12-07 garbage delete
2024-12-22 C10 modified

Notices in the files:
parts and their libraries:
COPYRIGHT: Copyright (C) 2022 Ultra Librarian. All rights reserved.
COPYRIGHT: Copyright (C) 2023 Ultra Librarian. All rights reserved.
